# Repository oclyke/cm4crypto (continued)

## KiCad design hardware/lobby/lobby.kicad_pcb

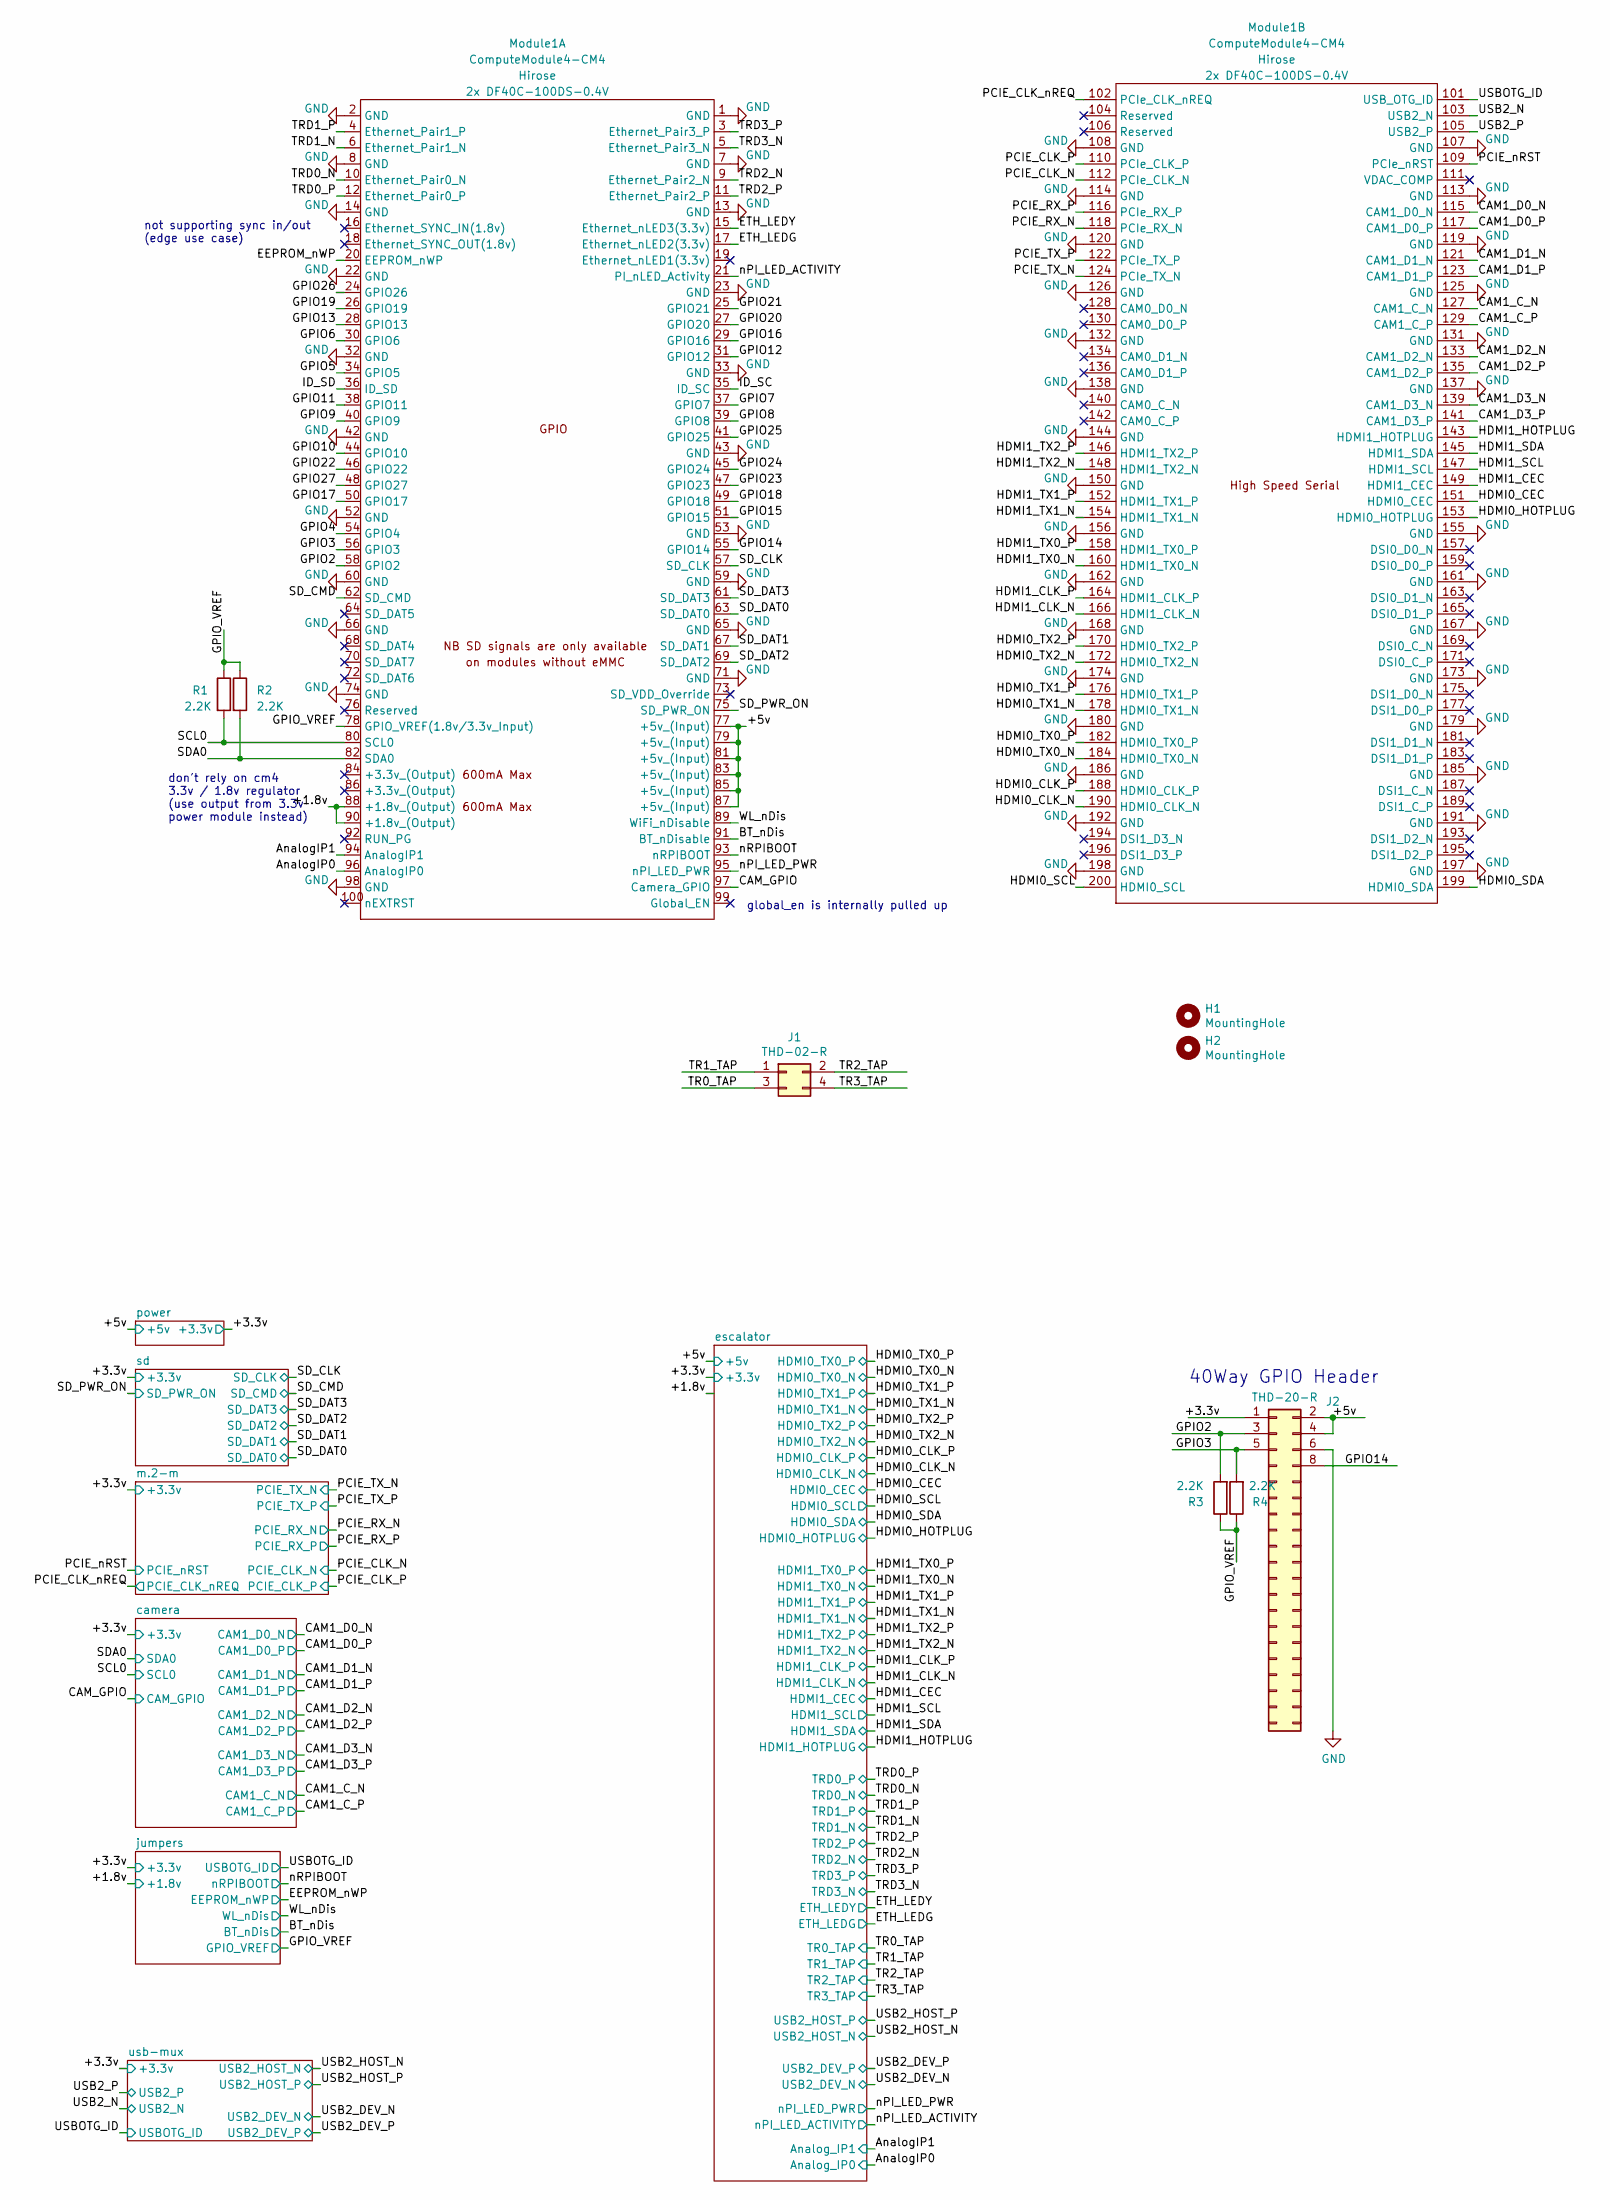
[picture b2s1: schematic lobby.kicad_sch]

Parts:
H1, H2: MountingHole; MountingHole_2.7mm_M2.5
J1: THD-02-R; PinHeader_2x02_P2.54mm_Vertical; Part Description PinHeader_2x02_P2.54mm_Vertical
J2: THD-20-R; rpi-40-just-power; Part Description PinHeader_2x20_P2.54mm_Vertical
Module1: ComputeModule4-CM4; Raspberry-Pi-4-Compute-Module-diagonal-mount-bl-ur
R1, R2, R3, R4: 2.2K; R_0603_1608Metric

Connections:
/+1.8v: Module1.88 (+1.8v_(Output)), Module1.90 (+1.8v_(Output)); also elsewhere on the board
/+3.3v: J2.1; also elsewhere on the board
/+5v: J2.2, J2.4, Module1.77 (+5v_(Input)), Module1.79 (+5v_(Input)), Module1.81 (+5v_(Input)), Module1.83 (+5v_(Input)), Module1.85 (+5v_(Input)), Module1.87 (+5v_(Input)); also elsewhere on the board
/AnalogIP0: Module1.96 (AnalogIP0); also elsewhere on the board
/AnalogIP1: Module1.94 (AnalogIP1); also elsewhere on the board
/BT_nDis: Module1.91 (BT_nDisable); also elsewhere on the board
/CAM1_C_N: Module1.127 (CAM1_C_N); also elsewhere on the board
/CAM1_C_P: Module1.129 (CAM1_C_P); also elsewhere on the board
/CAM1_D0_N: Module1.115 (CAM1_D0_N); also elsewhere on the board
/CAM1_D0_P: Module1.117 (CAM1_D0_P); also elsewhere on the board
/CAM1_D1_N: Module1.121 (CAM1_D1_N); also elsewhere on the board
/CAM1_D1_P: Module1.123 (CAM1_D1_P); also elsewhere on the board
/CAM1_D2_N: Module1.133 (CAM1_D2_N); also elsewhere on the board
/CAM1_D2_P: Module1.135 (CAM1_D2_P); also elsewhere on the board
/CAM1_D3_N: Module1.139 (CAM1_D3_N); also elsewhere on the board
/CAM1_D3_P: Module1.141 (CAM1_D3_P); also elsewhere on the board
/CAM_GPIO: Module1.97 (Camera_GPIO); also elsewhere on the board
/EEPROM_nWP: Module1.20 (EEPROM_nWP); also elsewhere on the board
/ETH_LEDG: Module1.17 (Ethernet_nLED2(3.3v)); also elsewhere on the board
/ETH_LEDY: Module1.15 (Ethernet_nLED3(3.3v)); also elsewhere on the board
/GPIO2: J2.3, Module1.58 (GPIO2), R3.2
/GPIO3: J2.5, Module1.56 (GPIO3), R4.2
/GPIO4: Module1.54 (GPIO4)
/GPIO5: Module1.34 (GPIO5)
/GPIO6: Module1.30 (GPIO6)
/GPIO7: Module1.37 (GPIO7)
/GPIO8: Module1.39 (GPIO8)
/GPIO9: Module1.40 (GPIO9)
/GPIO10: Module1.44 (GPIO10)
/GPIO11: Module1.38 (GPIO11)
/GPIO12: Module1.31 (GPIO12)
/GPIO13: Module1.28 (GPIO13)
/GPIO14: J2.8, Module1.55 (GPIO14)
/GPIO15: Module1.51 (GPIO15)
/GPIO16: Module1.29 (GPIO16)
/GPIO17: Module1.50 (GPIO17)
/GPIO18: Module1.49 (GPIO18)
/GPIO19: Module1.26 (GPIO19)
/GPIO20: Module1.27 (GPIO20)
/GPIO21: Module1.25 (GPIO21)
/GPIO22: Module1.46 (GPIO22)
/GPIO23: Module1.47 (GPIO23)
/GPIO24: Module1.45 (GPIO24)
/GPIO25: Module1.41 (GPIO25)
/GPIO26: Module1.24 (GPIO26)
/GPIO27: Module1.48 (GPIO27)
/GPIO_VREF: Module1.78 (GPIO_VREF(1.8v/3.3v_Input)), R1.1, R2.1, R3.1, R4.1; also elsewhere on the board
/HDMI0_CEC: Module1.151 (HDMI0_CEC); also elsewhere on the board
/HDMI0_CLK_N: Module1.190 (HDMI0_CLK_N); also elsewhere on the board
/HDMI0_CLK_P: Module1.188 (HDMI0_CLK_P); also elsewhere on the board
/HDMI0_HOTPLUG: Module1.153 (HDMI0_HOTPLUG); also elsewhere on the board
/HDMI0_SCL: Module1.200 (HDMI0_SCL); also elsewhere on the board
/HDMI0_SDA: Module1.199 (HDMI0_SDA); also elsewhere on the board
/HDMI0_TX0_N: Module1.184 (HDMI0_TX0_N); also elsewhere on the board
/HDMI0_TX0_P: Module1.182 (HDMI0_TX0_P); also elsewhere on the board
/HDMI0_TX1_N: Module1.178 (HDMI0_TX1_N); also elsewhere on the board
/HDMI0_TX1_P: Module1.176 (HDMI0_TX1_P); also elsewhere on the board
/HDMI0_TX2_N: Module1.172 (HDMI0_TX2_N); also elsewhere on the board
/HDMI0_TX2_P: Module1.170 (HDMI0_TX2_P); also elsewhere on the board
/HDMI1_CEC: Module1.149 (HDMI1_CEC); also elsewhere on the board
/HDMI1_CLK_N: Module1.166 (HDMI1_CLK_N); also elsewhere on the board
/HDMI1_CLK_P: Module1.164 (HDMI1_CLK_P); also elsewhere on the board
/HDMI1_HOTPLUG: Module1.143 (HDMI1_HOTPLUG); also elsewhere on the board
/HDMI1_SCL: Module1.147 (HDMI1_SCL); also elsewhere on the board
/HDMI1_SDA: Module1.145 (HDMI1_SDA); also elsewhere on the board
/HDMI1_TX0_N: Module1.160 (HDMI1_TX0_N); also elsewhere on the board
/HDMI1_TX0_P: Module1.158 (HDMI1_TX0_P); also elsewhere on the board
/HDMI1_TX1_N: Module1.154 (HDMI1_TX1_N); also elsewhere on the board
/HDMI1_TX1_P: Module1.152 (HDMI1_TX1_P); also elsewhere on the board
/HDMI1_TX2_N: Module1.148 (HDMI1_TX2_N); also elsewhere on the board
/HDMI1_TX2_P: Module1.146 (HDMI1_TX2_P); also elsewhere on the board
/ID_SC: Module1.35 (ID_SC)
/ID_SD: Module1.36 (ID_SD)
/PCIE_CLK_N: Module1.112 (PCIe_CLK_N); also elsewhere on the board
/PCIE_CLK_P: Module1.110 (PCIe_CLK_P); also elsewhere on the board
/PCIE_CLK_nREQ: Module1.102 (PCIe_CLK_nREQ); also elsewhere on the board
/PCIE_RX_N: Module1.118 (PCIe_RX_N); also elsewhere on the board
/PCIE_RX_P: Module1.116 (PCIe_RX_P); also elsewhere on the board
/PCIE_TX_N: Module1.124 (PCIe_TX_N); also elsewhere on the board
/PCIE_TX_P: Module1.122 (PCIe_TX_P); also elsewhere on the board
/PCIE_nRST: Module1.109 (PCIe_nRST); also elsewhere on the board
/SCL0: Module1.80 (SCL0), R1.2; also elsewhere on the board
/SDA0: Module1.82 (SDA0), R2.2; also elsewhere on the board
/SD_CLK: Module1.57 (SD_CLK); also elsewhere on the board
/SD_CMD: Module1.62 (SD_CMD); also elsewhere on the board
/SD_DAT0: Module1.63 (SD_DAT0); also elsewhere on the board
/SD_DAT1: Module1.67 (SD_DAT1); also elsewhere on the board
/SD_DAT2: Module1.69 (SD_DAT2); also elsewhere on the board
/SD_DAT3: Module1.61 (SD_DAT3); also elsewhere on the board
/SD_PWR_ON: Module1.75 (SD_PWR_ON); also elsewhere on the board
/TR0_TAP: J1.3; also elsewhere on the board
/TR1_TAP: J1.1; also elsewhere on the board
/TR2_TAP: J1.2; also elsewhere on the board
/TR3_TAP: J1.4; also elsewhere on the board
/TRD0_N: Module1.10 (Ethernet_Pair0_N); also elsewhere on the board
/TRD0_P: Module1.12 (Ethernet_Pair0_P); also elsewhere on the board
/TRD1_N: Module1.6 (Ethernet_Pair1_N); also elsewhere on the board
/TRD1_P: Module1.4 (Ethernet_Pair1_P); also elsewhere on the board
/TRD2_N: Module1.9 (Ethernet_Pair2_N); also elsewhere on the board
/TRD2_P: Module1.11 (Ethernet_Pair2_P); also elsewhere on the board
/TRD3_N: Module1.5 (Ethernet_Pair3_N); also elsewhere on the board
/TRD3_P: Module1.3 (Ethernet_Pair3_P); also elsewhere on the board
/USB2_N: Module1.103 (USB2_N); also elsewhere on the board
/USB2_P: Module1.105 (USB2_P); also elsewhere on the board
/USBOTG_ID: Module1.101 (USB_OTG_ID); also elsewhere on the board
/WL_nDis: Module1.89 (WiFi_nDisable); also elsewhere on the board
/nPI_LED_ACTIVITY: Module1.21 (PI_nLED_Activity); also elsewhere on the board
/nPI_LED_PWR: Module1.95 (nPI_LED_PWR); also elsewhere on the board
/nRPIBOOT: Module1.93 (nRPIBOOT); also elsewhere on the board
GND: J2.6, Module1.1 (GND), Module1.2 (GND), Module1.7 (GND), Module1.8 (GND), Module1.13 (GND), Module1.14 (GND), Module1.22 (GND), Module1.23 (GND), Module1.32 (GND), Module1.33 (GND), Module1.42 (GND), Module1.43 (GND), Module1.52 (GND), Module1.53 (GND), Module1.59 (GND), Module1.60 (GND), Module1.65 (GND), Module1.66 (GND), Module1.71 (GND), Module1.74 (GND), Module1.98 (GND), Module1.107 (GND), Module1.108 (GND), Module1.113 (GND), Module1.114 (GND), Module1.119 (GND), Module1.120 (GND), Module1.125 (GND), Module1.126 (GND), Module1.131 (GND), Module1.132 (GND), Module1.137 (GND), Module1.138 (GND), Module1.144 (GND), Module1.150 (GND), Module1.155 (GND), Module1.156 (GND), Module1.161 (GND), Module1.162 (GND), Module1.167 (GND), Module1.168 (GND), Module1.173 (GND), Module1.174 (GND), Module1.179 (GND), Module1.180 (GND), Module1.185 (GND), Module1.186 (GND), Module1.191 (GND), Module1.192 (GND), Module1.197 (GND), Module1.198 (GND); also elsewhere on the board

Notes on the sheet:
not supporting sync in/out (edge use case)
don't rely on cm4 3.3v / 1.8v regulator (use output from 3.3v power module instead)
global_en is internally pulled up
40Way GPIO Header

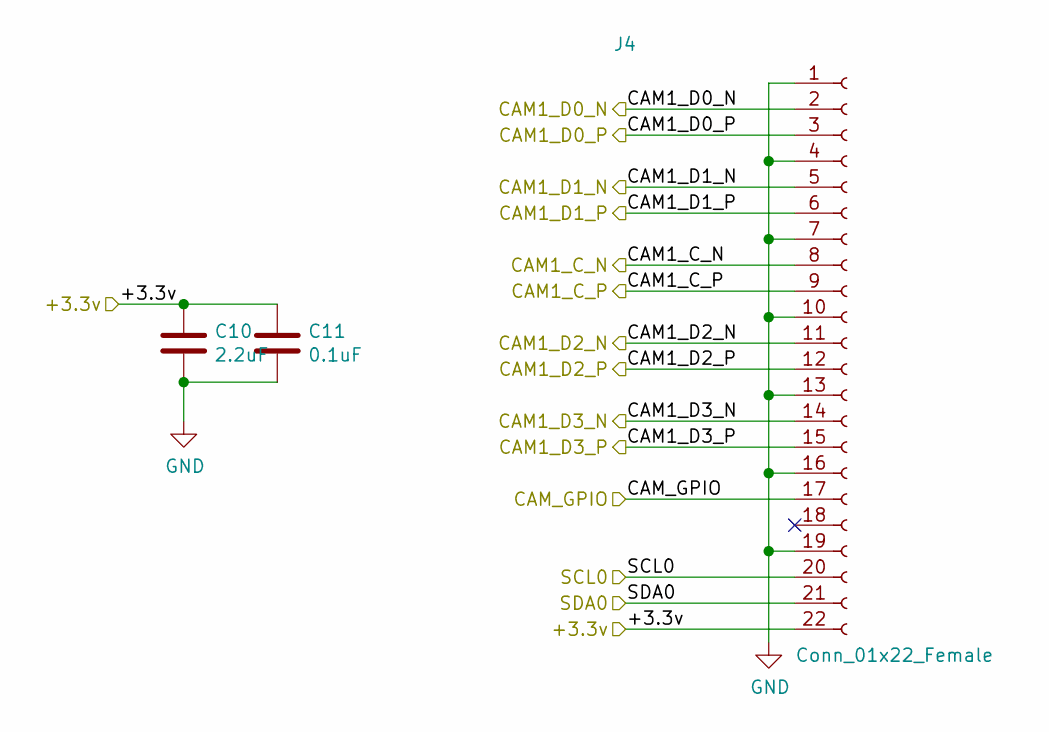
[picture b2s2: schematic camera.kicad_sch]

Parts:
C10: 2.2uF; C_0603_1608Metric; Part Description 10uF 10% 10V Ceramic Capacitor X7R 0805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
C11: 0.1uF; C_0603_1608Metric; Part Description 10uF 10% 10V Ceramic Capacitor X7R 0805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
J4: Conn_01x22_Female; SFV22R-2STE1HLF; Part Description 22 Position FFC, FPC Connector Contacts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

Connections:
/+3.3v: C10.1, C11.1, J4.22; also elsewhere on the board
/CAM1_C_N: J4.8; also elsewhere on the board
/CAM1_C_P: J4.9; also elsewhere on the board
/CAM1_D0_N: J4.2; also elsewhere on the board
/CAM1_D0_P: J4.3; also elsewhere on the board
/CAM1_D1_N: J4.5; also elsewhere on the board
/CAM1_D1_P: J4.6; also elsewhere on the board
/CAM1_D2_N: J4.11; also elsewhere on the board
/CAM1_D2_P: J4.12; also elsewhere on the board
/CAM1_D3_N: J4.14; also elsewhere on the board
/CAM1_D3_P: J4.15; also elsewhere on the board
/CAM_GPIO: J4.17; also elsewhere on the board
/SCL0: J4.20; also elsewhere on the board
/SDA0: J4.21; also elsewhere on the board
GND: C10.2, C11.2, J4.1, J4.4, J4.7, J4.10, J4.13, J4.16, J4.19; also elsewhere on the board

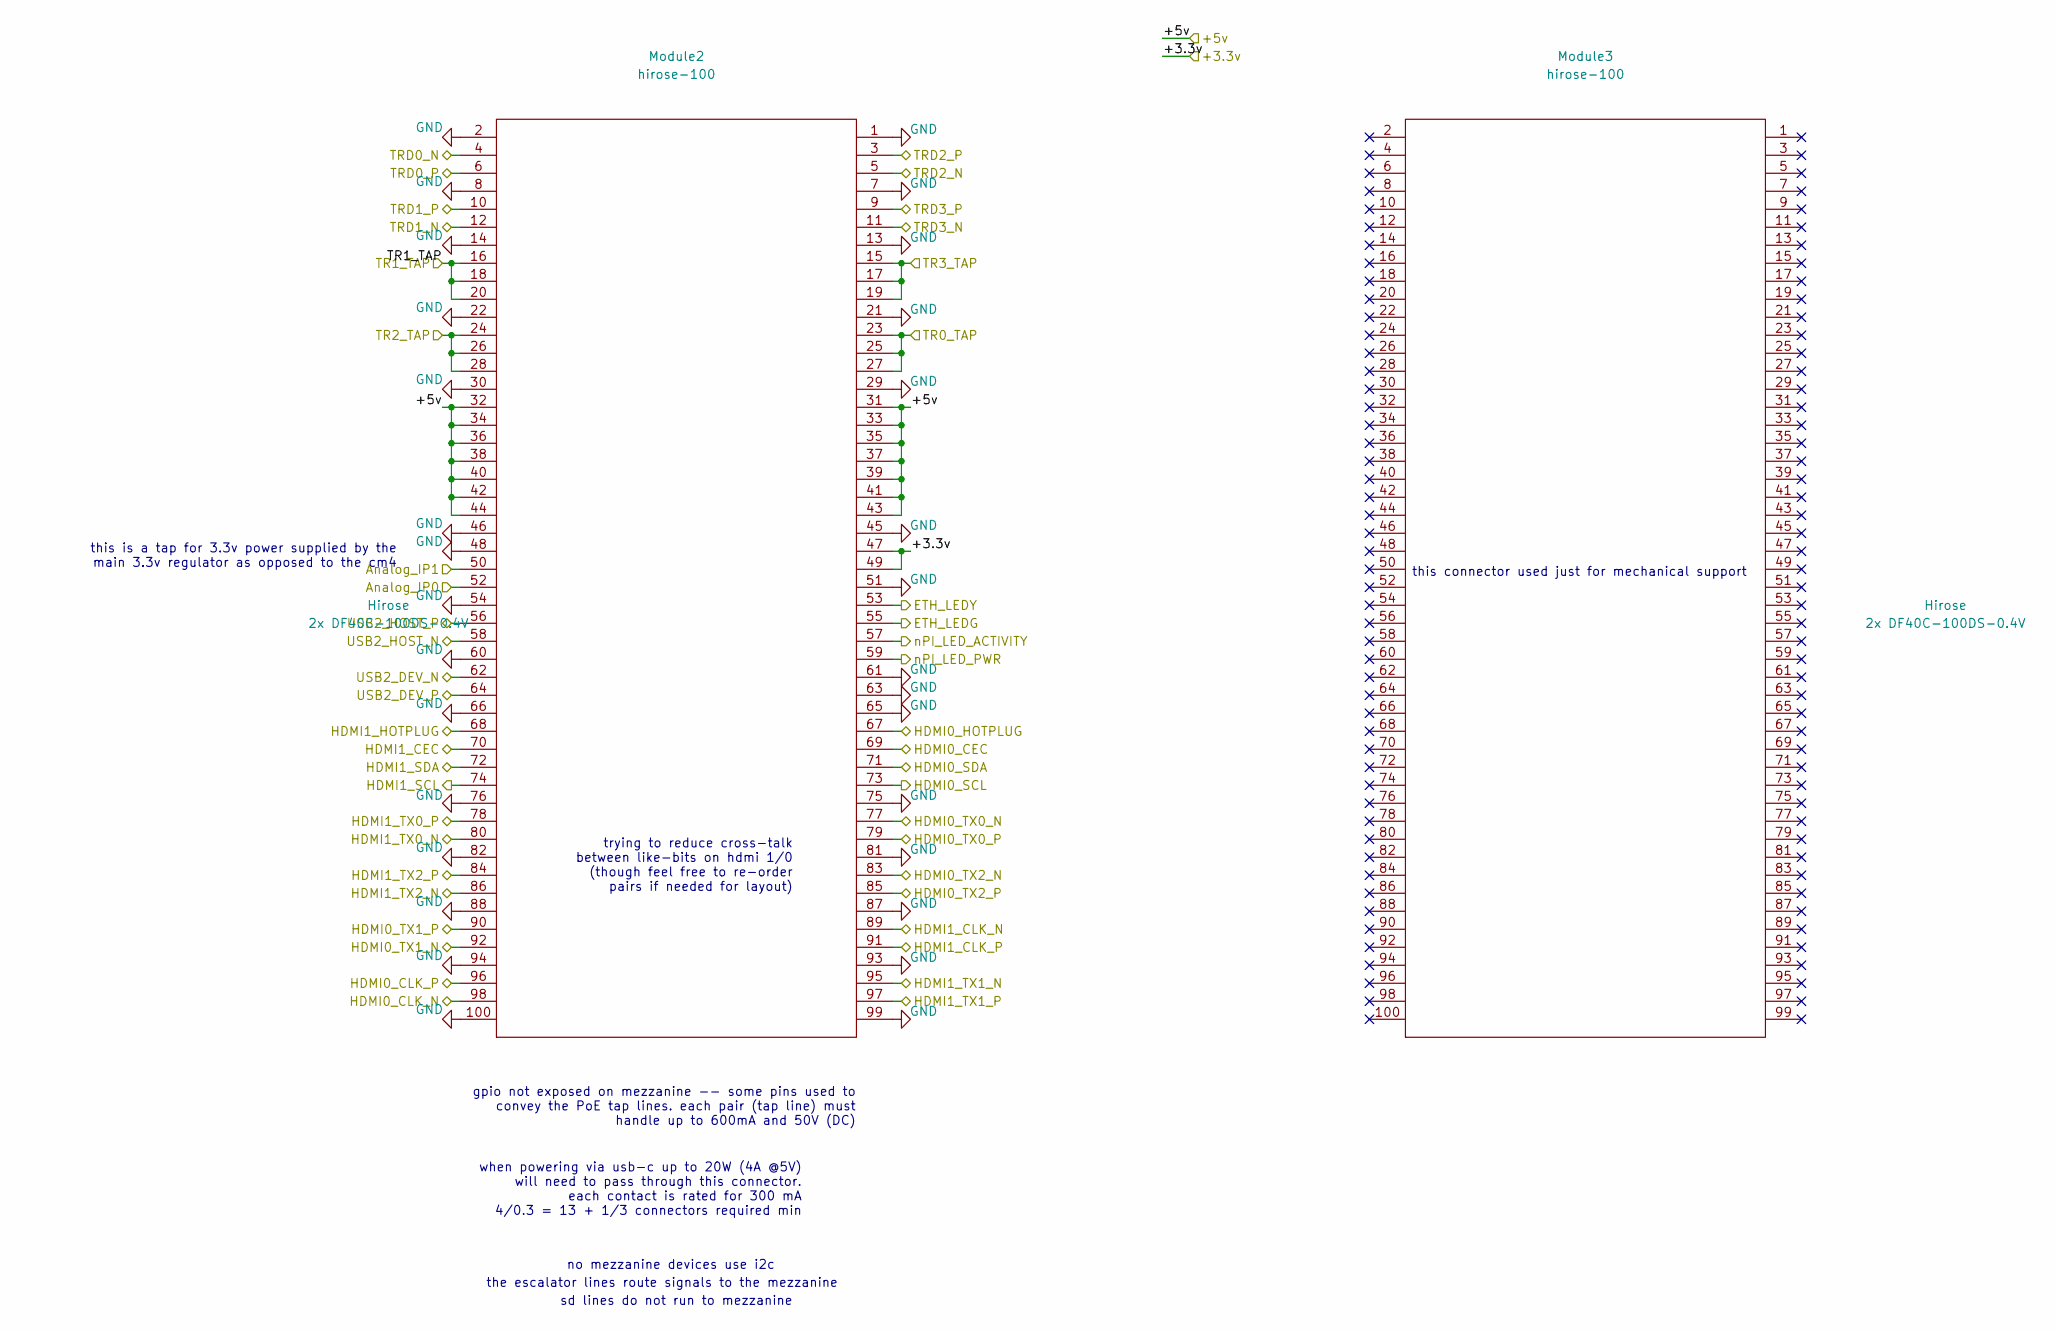
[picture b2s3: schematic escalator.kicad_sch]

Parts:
Module2, Module3: hirose-100; DF40C-100DS-0.4V(51)

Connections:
/+3.3v: Module2.47, Module2.49; also elsewhere on the board
/+5v: Module2.31, Module2.32, Module2.33, Module2.34, Module2.35, Module2.36, Module2.37, Module2.38, Module2.39, Module2.40, Module2.41, Module2.42, Module2.43, Module2.44; also elsewhere on the board
/AnalogIP0: Module2.52; also elsewhere on the board
/AnalogIP1: Module2.50; also elsewhere on the board
/ETH_LEDG: Module2.55; also elsewhere on the board
/ETH_LEDY: Module2.53; also elsewhere on the board
/HDMI0_CEC: Module2.69; also elsewhere on the board
/HDMI0_CLK_N: Module2.98; also elsewhere on the board
/HDMI0_CLK_P: Module2.96; also elsewhere on the board
/HDMI0_HOTPLUG: Module2.67; also elsewhere on the board
/HDMI0_SCL: Module2.73; also elsewhere on the board
/HDMI0_SDA: Module2.71; also elsewhere on the board
/HDMI0_TX0_N: Module2.77; also elsewhere on the board
/HDMI0_TX0_P: Module2.79; also elsewhere on the board
/HDMI0_TX1_N: Module2.92; also elsewhere on the board
/HDMI0_TX1_P: Module2.90; also elsewhere on the board
/HDMI0_TX2_N: Module2.83; also elsewhere on the board
/HDMI0_TX2_P: Module2.85; also elsewhere on the board
/HDMI1_CEC: Module2.70; also elsewhere on the board
/HDMI1_CLK_N: Module2.89; also elsewhere on the board
/HDMI1_CLK_P: Module2.91; also elsewhere on the board
/HDMI1_HOTPLUG: Module2.68; also elsewhere on the board
/HDMI1_SCL: Module2.74; also elsewhere on the board
/HDMI1_SDA: Module2.72; also elsewhere on the board
/HDMI1_TX0_N: Module2.80; also elsewhere on the board
/HDMI1_TX0_P: Module2.78; also elsewhere on the board
/HDMI1_TX1_N: Module2.95; also elsewhere on the board
/HDMI1_TX1_P: Module2.97; also elsewhere on the board
/HDMI1_TX2_N: Module2.86; also elsewhere on the board
/HDMI1_TX2_P: Module2.84; also elsewhere on the board
/TR0_TAP: Module2.23, Module2.25, Module2.27; also elsewhere on the board
/TR1_TAP: Module2.16, Module2.18, Module2.20; also elsewhere on the board
/TR2_TAP: Module2.24, Module2.26, Module2.28; also elsewhere on the board
/TR3_TAP: Module2.15, Module2.17, Module2.19; also elsewhere on the board
/TRD0_N: Module2.4; also elsewhere on the board
/TRD0_P: Module2.6; also elsewhere on the board
/TRD1_N: Module2.12; also elsewhere on the board
/TRD1_P: Module2.10; also elsewhere on the board
/TRD2_N: Module2.5; also elsewhere on the board
/TRD2_P: Module2.3; also elsewhere on the board
/TRD3_N: Module2.11; also elsewhere on the board
/TRD3_P: Module2.9; also elsewhere on the board
/USB2_DEV_N: Module2.62; also elsewhere on the board
/USB2_DEV_P: Module2.64; also elsewhere on the board
/USB2_HOST_N: Module2.58; also elsewhere on the board
/USB2_HOST_P: Module2.56; also elsewhere on the board
/nPI_LED_ACTIVITY: Module2.57; also elsewhere on the board
/nPI_LED_PWR: Module2.59; also elsewhere on the board
GND: Module2.1, Module2.2, Module2.7, Module2.8, Module2.13, Module2.14, Module2.21, Module2.22, Module2.29, Module2.30, Module2.45, Module2.46, Module2.48, Module2.51, Module2.54, Module2.60, Module2.61, Module2.63, Module2.65, Module2.66, Module2.75, Module2.76, Module2.81, Module2.82, Module2.87, Module2.88, Module2.93, Module2.94, Module2.99, Module2.100; also elsewhere on the board

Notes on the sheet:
this is a tap for 3.3v power supplied by the main 3.3v regulator as opposed to the cm4
sd lines do not run to mezzanine
no mezzanine devices use i2c
trying to reduce cross-talk between like-bits on hdmi 1/0 (though feel free to re-order pairs if needed for layout)
when powering via usb-c up to 20W (4A @5V) will need to pass through this connector. each contact is rated for 300 mA 4/0.3 = 13 + 1/3 connectors required min
the escalator lines route signals to the mezzanine
gpio not exposed on mezzanine -- some pins used to convey the PoE tap lines. each pair (tap line) must handle up to 600mA and 50V (DC)
this connector used just for mechanical support

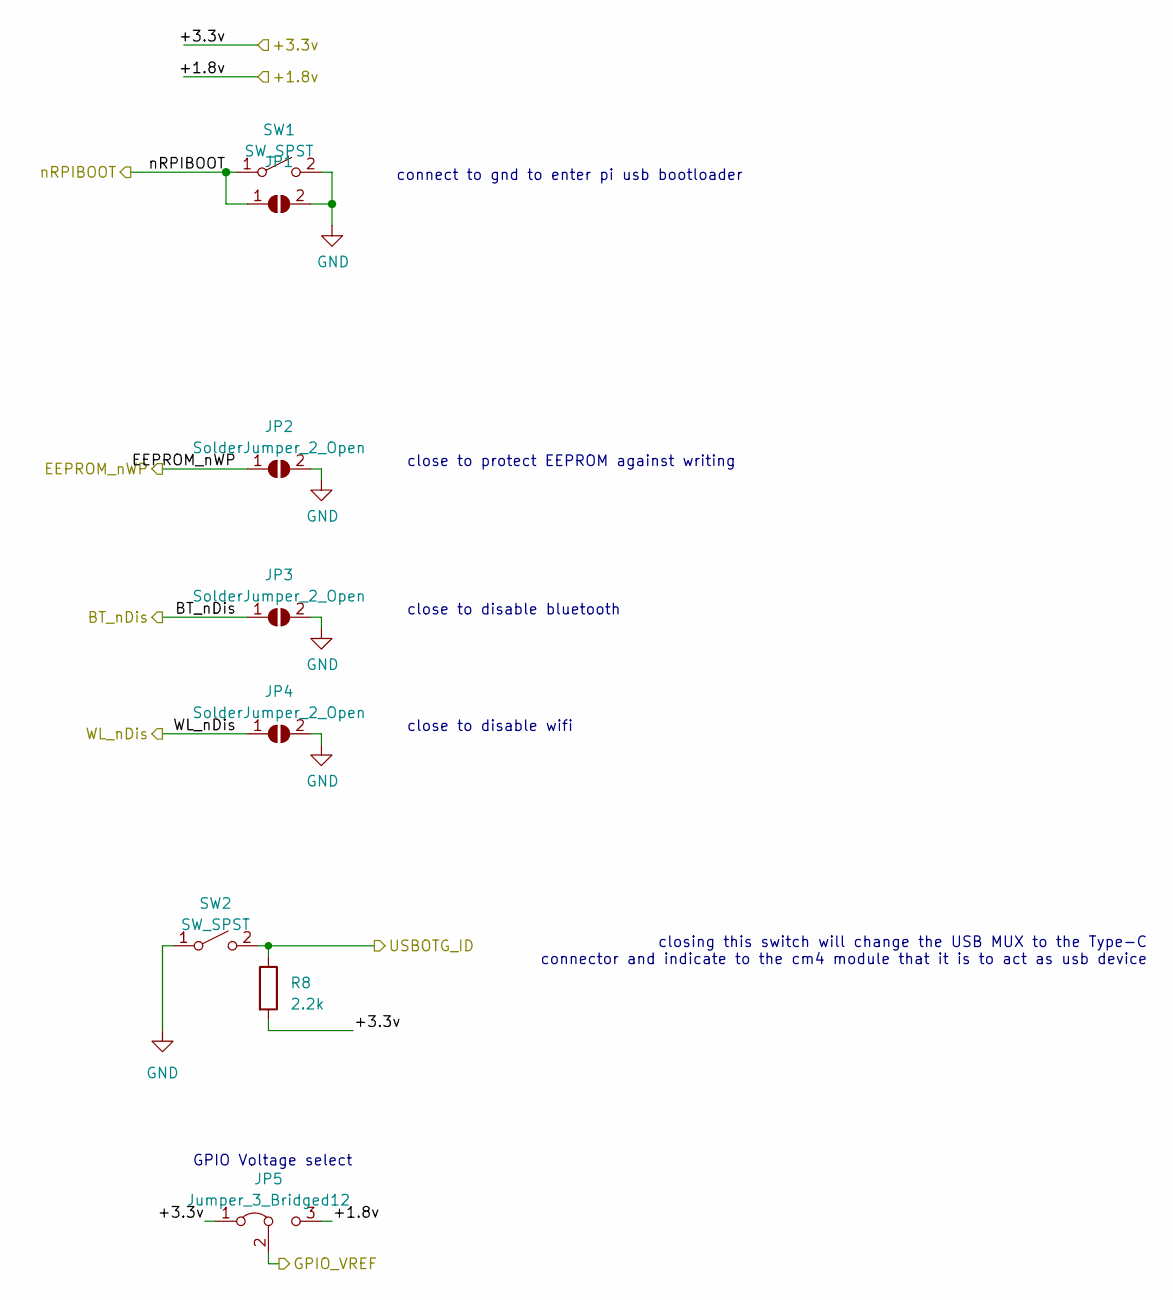
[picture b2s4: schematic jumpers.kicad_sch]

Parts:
JP1, JP2, JP3, JP4: SolderJumper_2_Open; SolderJumper-2_P1.3mm_Open_RoundedPad1.0x1.5mm
JP5: Jumper_3_Bridged12; SolderJumper-3_P1.3mm_Bridged12_RoundedPad1.0x1.5mm
R8: 2.2k; R_0603_1608Metric
SW1, SW2: SW_SPST; cus-12b

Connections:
/+1.8v: JP5.3 (B); also elsewhere on the board
/+3.3v: JP5.1 (A), R8.2; also elsewhere on the board
/BT_nDis: JP3.1 (A); also elsewhere on the board
/EEPROM_nWP: JP2.1 (A); also elsewhere on the board
/GPIO_VREF: JP5.2 (C); also elsewhere on the board
/USBOTG_ID: R8.1, SW2.2 (B); also elsewhere on the board
/WL_nDis: JP4.1 (A); also elsewhere on the board
/nRPIBOOT: JP1.1 (A), SW1.1 (A); also elsewhere on the board
GND: JP1.2 (B), JP2.2 (B), JP3.2 (B), JP4.2 (B), SW1.2 (B), SW2.1 (A); also elsewhere on the board

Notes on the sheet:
GPIO Voltage select
connect to gnd to enter pi usb bootloader
close to protect EEPROM against writing
close to disable bluetooth
close to disable wifi
closing this switch will change the USB MUX to the Type-C connector and indicate to the cm4 module that it is to act as usb device

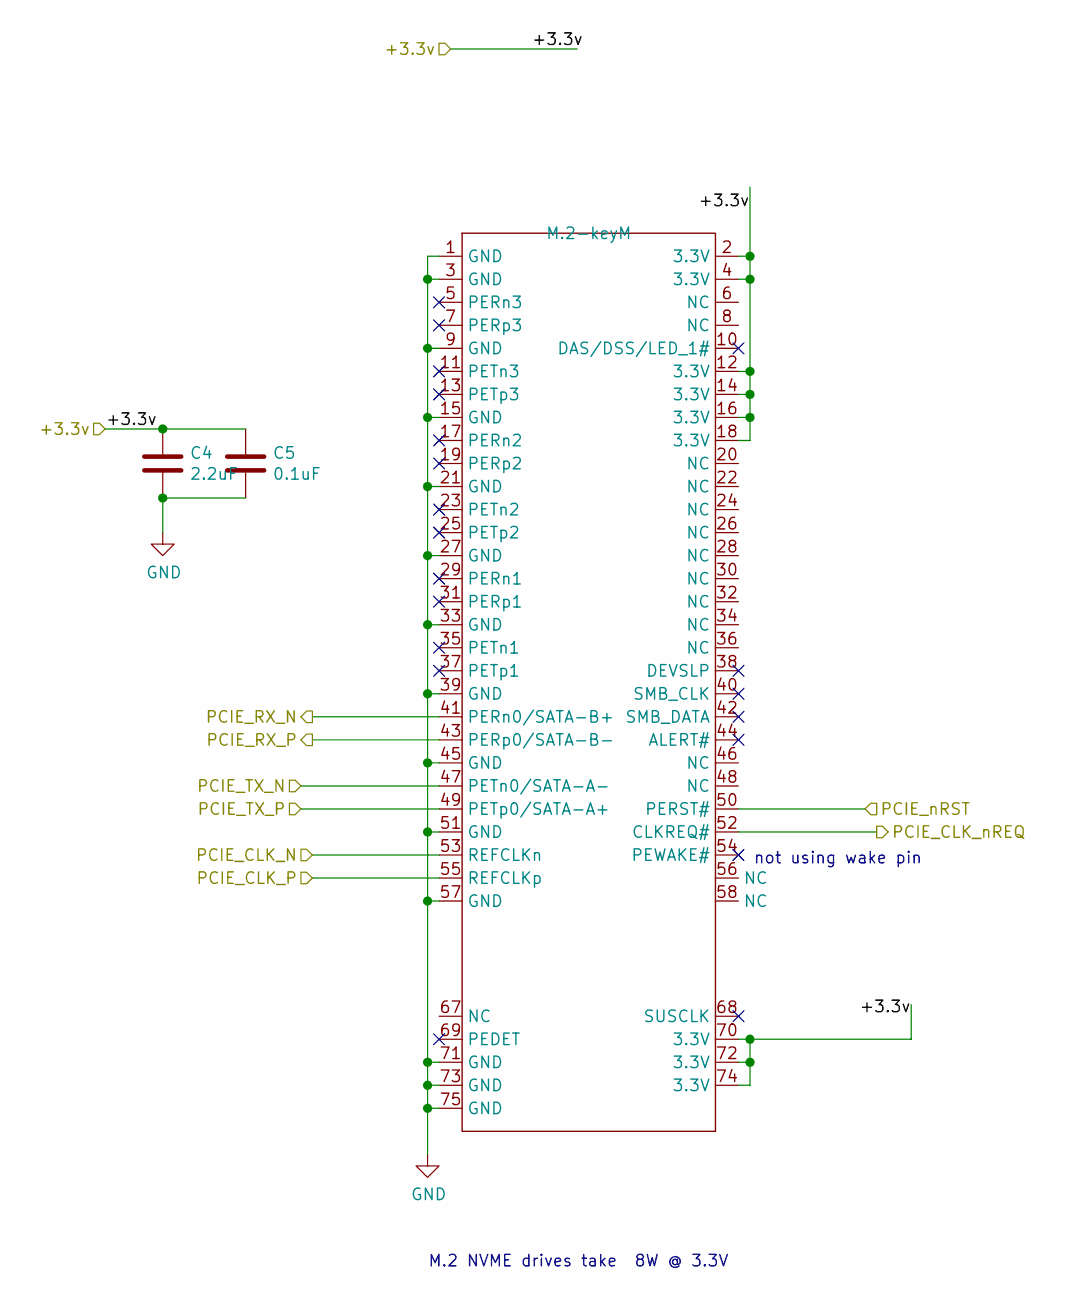
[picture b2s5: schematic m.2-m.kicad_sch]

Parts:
C4: 2.2uF; C_0603_1608Metric; Part Description 10uF 10% 10V Ceramic Capacitor X7R 0805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
C5: 0.1uF; C_0603_1608Metric; Part Description 10uF 10% 10V Ceramic Capacitor X7R 0805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
U2: M.2-keyM; M.2 - M - Amphenol - 10131758-001RLF

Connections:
/+3.3v: C4.1, C5.1, U2.2 (3.3V), U2.4 (3.3V), U2.12 (3.3V), U2.14 (3.3V), U2.16 (3.3V), U2.18 (3.3V), U2.70 (3.3V), U2.72 (3.3V), U2.74 (3.3V); also elsewhere on the board
/PCIE_CLK_N: U2.53 (REFCLKn); also elsewhere on the board
/PCIE_CLK_P: U2.55 (REFCLKp); also elsewhere on the board
/PCIE_CLK_nREQ: U2.52 (CLKREQ#); also elsewhere on the board
/PCIE_RX_N: U2.41 (PERn0/SATA-B+); also elsewhere on the board
/PCIE_RX_P: U2.43 (PERp0/SATA-B-); also elsewhere on the board
/PCIE_TX_N: U2.47 (PETn0/SATA-A-); also elsewhere on the board
/PCIE_TX_P: U2.49 (PETp0/SATA-A+); also elsewhere on the board
/PCIE_nRST: U2.50 (PERST#); also elsewhere on the board
GND: C4.2, C5.2, U2.1 (GND), U2.3 (GND), U2.9 (GND), U2.15 (GND), U2.21 (GND), U2.27 (GND), U2.33 (GND), U2.39 (GND), U2.45 (GND), U2.51 (GND), U2.57 (GND), U2.71 (GND), U2.73 (GND), U2.75 (GND); also elsewhere on the board

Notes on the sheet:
M.2 NVME drives take ~ 8W @ 3.3V
not using wake pin

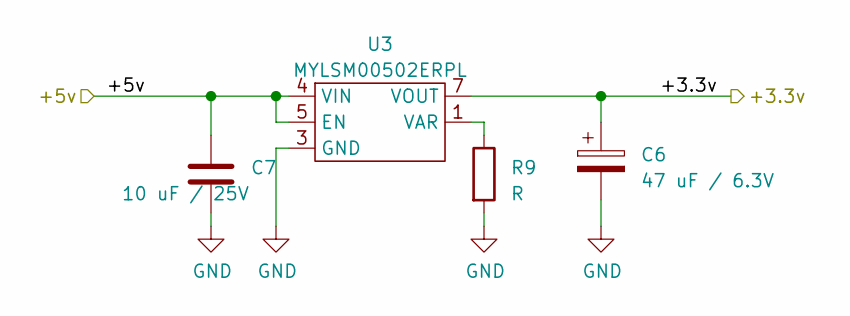
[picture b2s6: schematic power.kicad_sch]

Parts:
C6: 47 uF / 6.3V; CP_EIA-2012-15_AVX-P
C7: 10 uF / 25V; C_0603_1608Metric
R9: R; R_0603_1608Metric
U3: MYLSM00502ERPL

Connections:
/+3.3v: C6.1, U3.7 (VOUT); also elsewhere on the board
/+5v: C7.1, U3.4 (VIN), U3.5 (EN); also elsewhere on the board
GND: C6.2, C7.2, R9.2, U3.2 (GND), U3.3 (GND), U3.6 (GND), U3.8 (GND), U3.9 (GND); also elsewhere on the board
unnamed: R9.1, U3.1 (VAR)

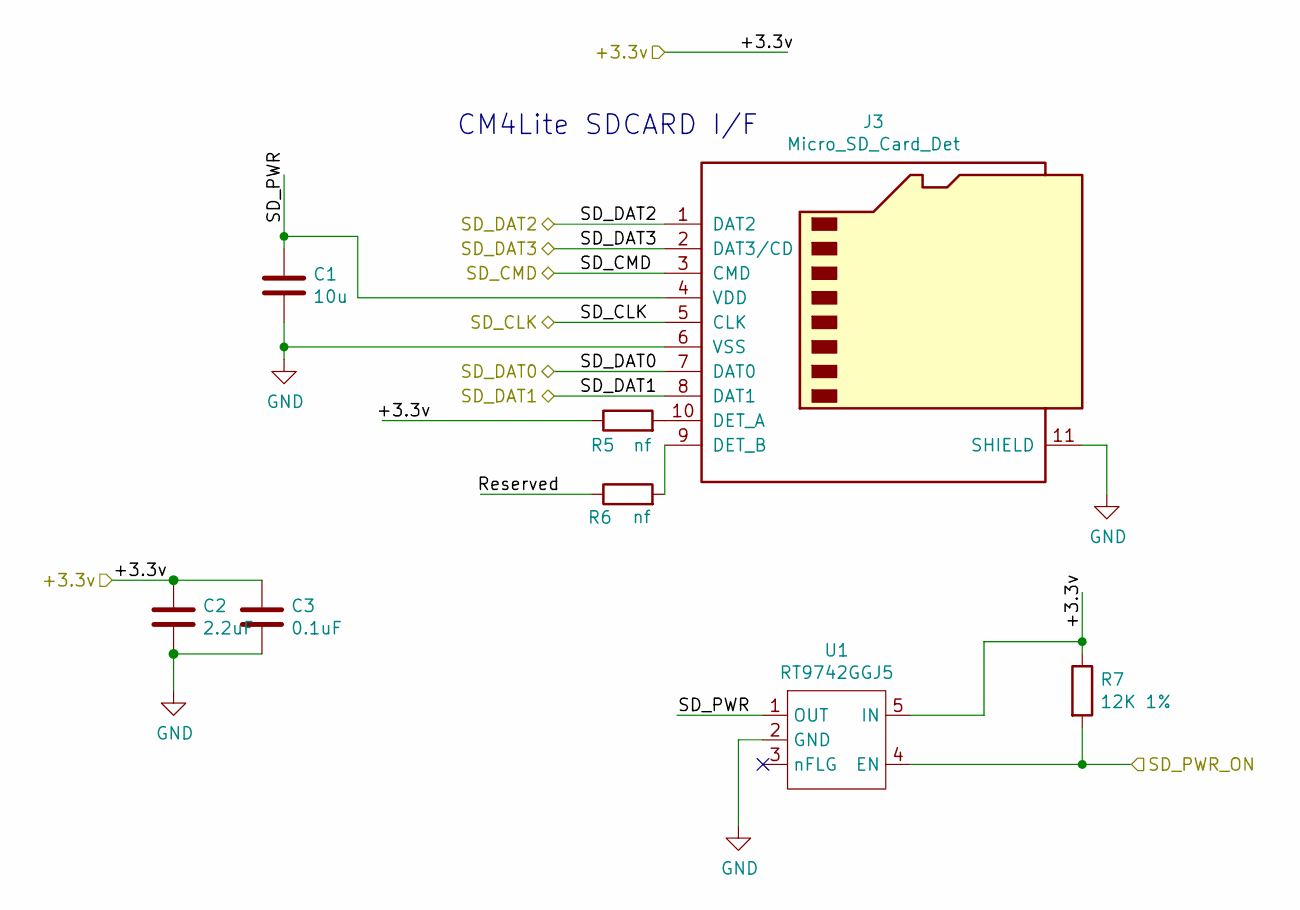
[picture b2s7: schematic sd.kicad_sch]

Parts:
C1: 10u; C_0603_1608Metric; Part Description 10uF 10% 10V Ceramic Capacitor X7R 0805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
C2: 2.2uF; C_0603_1608Metric; Part Description 10uF 10% 10V Ceramic Capacitor X7R 0805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
C3: 0.1uF; C_0603_1608Metric; Part Description 10uF 10% 10V Ceramic Capacitor X7R 0805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
J3: Micro_SD_Card_Det; amphenol-sd-push-pull_114-00841-68; Part Description 9 (8 + 1) Position Card Connector micro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
R5, R6: nf; R_0603_1608Metric; Part Description Resistor 1K M1005 1% 63mW
R7: 12K 1%; R_0603_1608Metric; Part Description Resistor 12K M1005 1% 63mW
U1: RT9742GGJ5; SOT-23-5; Part Description Power Switch/Driver 1:1 N-Channel 1A TS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

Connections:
/+3.3v: C2.1, C3.1, R5.1, R7.1, U1.5 (IN); also elsewhere on the board
/SD_CLK: J3.5 (CLK); also elsewhere on the board
/SD_CMD: J3.3 (CMD); also elsewhere on the board
/SD_DAT0: J3.7 (DAT0); also elsewhere on the board
/SD_DAT1: J3.8 (DAT1); also elsewhere on the board
/SD_DAT2: J3.1 (DAT2); also elsewhere on the board
/SD_DAT3: J3.2 (DAT3/CD); also elsewhere on the board
/SD_PWR_ON: R7.2, U1.4 (EN); also elsewhere on the board
/sd/Reserved: R6.1
/sd/SD_PWR: C1.1, J3.4 (VDD), U1.1 (OUT)
GND: C1.2, C2.2, C3.2, J3.6 (VSS), J3.11 (SHIELD), U1.2 (GND); also elsewhere on the board
unnamed: J3.9 (DET_B), R6.2
unnamed: J3.10 (DET_A), R5.2

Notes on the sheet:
CM4Lite SDCARD I/F

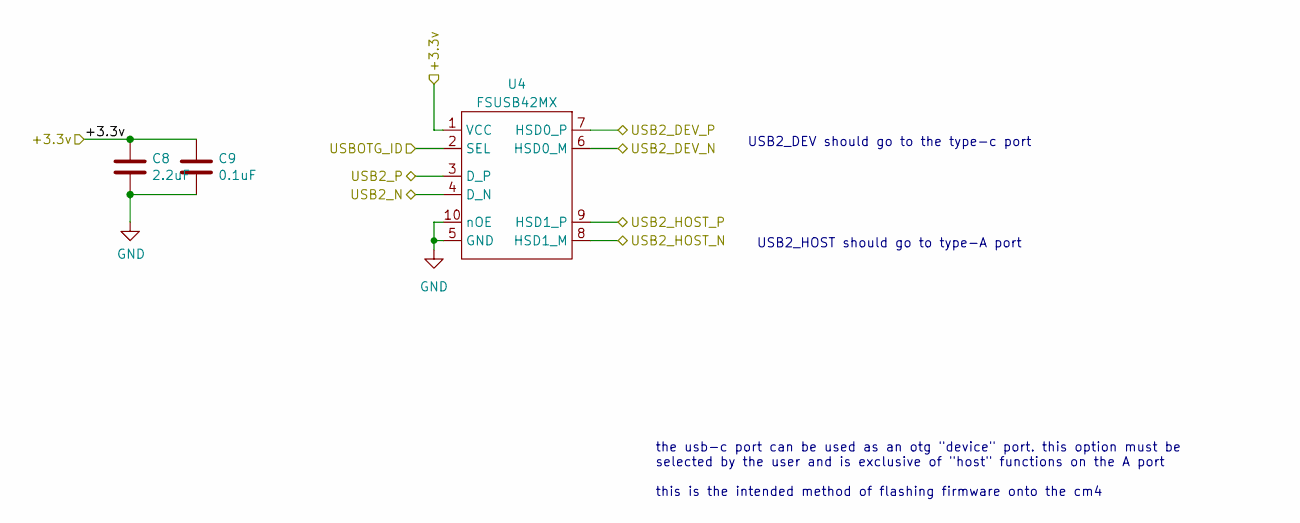
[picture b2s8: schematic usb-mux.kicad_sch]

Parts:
C8: 2.2uF; C_0603_1608Metric; Part Description 10uF 10% 10V Ceramic Capacitor X7R 0805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
C9: 0.1uF; C_0603_1608Metric; Part Description 10uF 10% 10V Ceramic Capacitor X7R 0805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
U4: FSUSB42MX; UQFN-10_1.6x2.1mm_P0.5mm

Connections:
/+3.3v: C8.1, C9.1, U4.1 (VCC); also elsewhere on the board
/USB2_DEV_N: U4.6 (HSD0_M); also elsewhere on the board
/USB2_DEV_P: U4.7 (HSD0_P); also elsewhere on the board
/USB2_HOST_N: U4.8 (HSD1_M); also elsewhere on the board
/USB2_HOST_P: U4.9 (HSD1_P); also elsewhere on the board
/USB2_N: U4.4 (D_N); also elsewhere on the board
/USB2_P: U4.3 (D_P); also elsewhere on the board
/USBOTG_ID: U4.2 (SEL); also elsewhere on the board
GND: C8.2, C9.2, U4.5 (GND), U4.10 (nOE); also elsewhere on the board

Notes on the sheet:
the usb-c port can be used as an otg "device" port. this option must be selected by the user and is exclusive of "host" functions on the A port this is the intended method of flashing firmware onto the cm4
USB2_DEV should go to the type-c port
USB2_HOST should go to type-A port
